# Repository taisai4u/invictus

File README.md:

# Invictus Flight Computer
A rocket flight computer capable of real-time sensor fusion, state estimation, and autonomous flight control.

Records absolute orientation during the duration of a rocket's flight

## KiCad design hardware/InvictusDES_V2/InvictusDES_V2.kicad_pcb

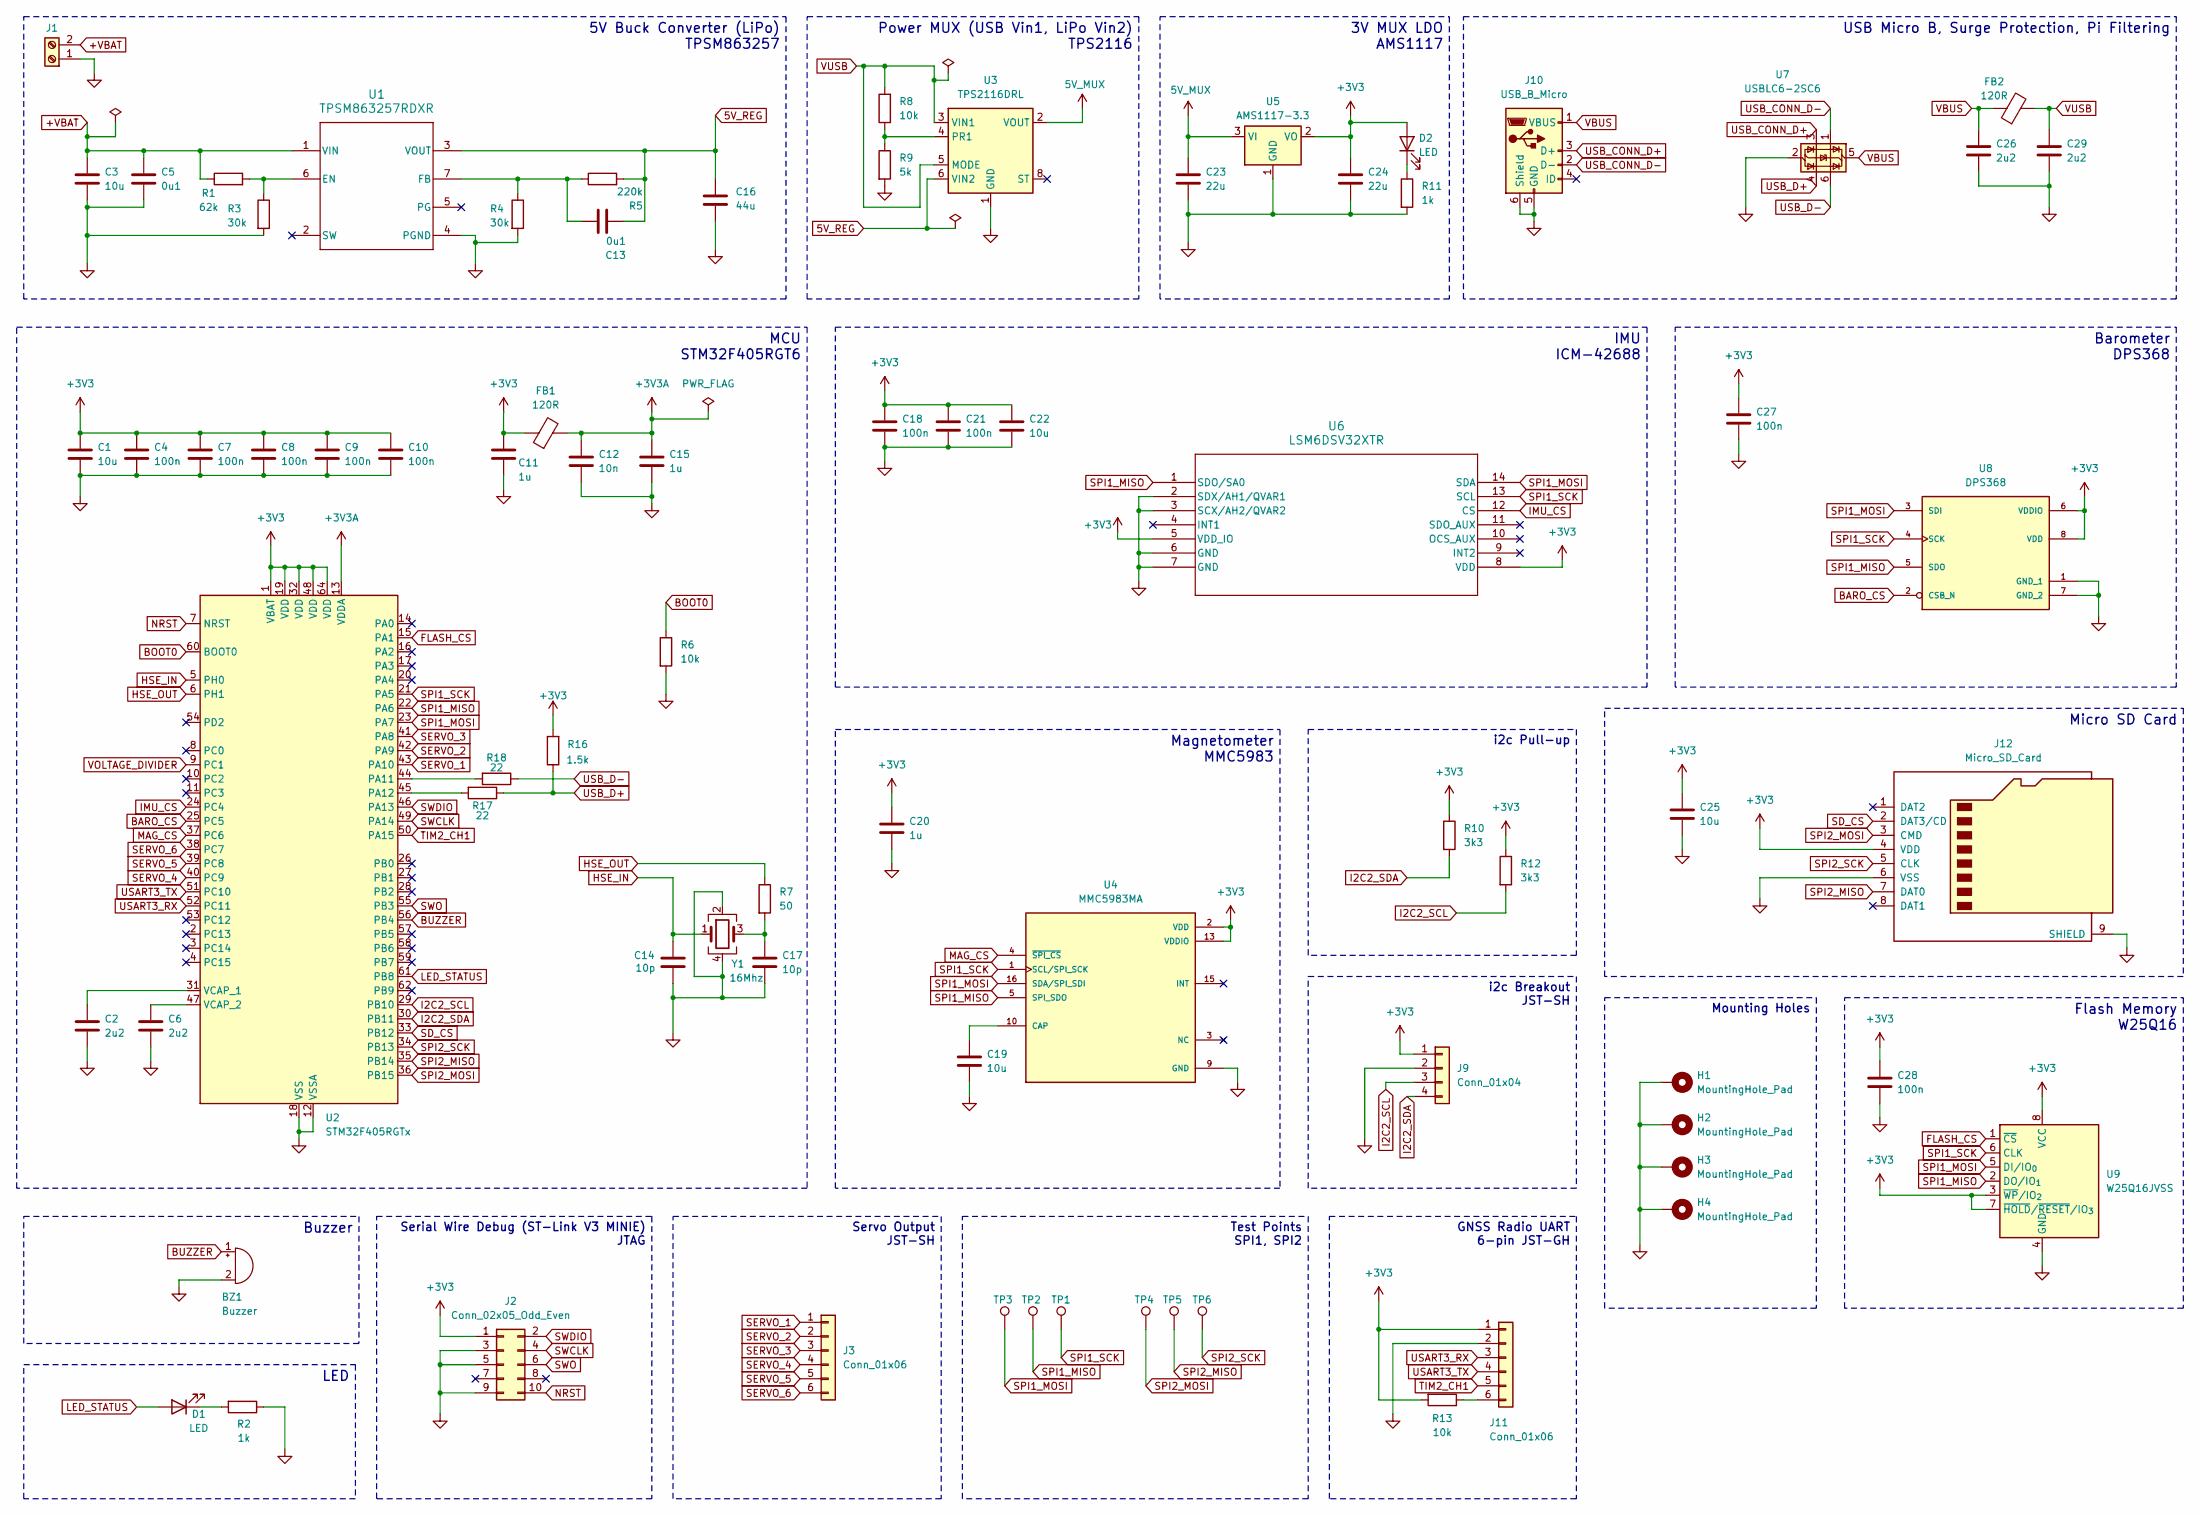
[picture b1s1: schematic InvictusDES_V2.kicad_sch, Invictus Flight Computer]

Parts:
BZ1: Buzzer; Buzzer_Murata_PKMCS0909E
C1, C3, C19: 10u; C_0603_1608Metric
C2, C6: 2u2; C_0603_1608Metric
C4, C7, C8, C9, C10, C18, C27, C28: 100n; C_0402_1005Metric
C5, C13: 0u1; C_0402_1005Metric
C11, C15, C20: 1u; C_0603_1608Metric
C12: 10n; C_0402_1005Metric
C14, C17: 10p; C_0603_1608Metric
C16: 44u; C_0402_1005Metric
C21: 100n; C_0603_1608Metric
C22, C25: 10u; C_0402_1005Metric
C23, C24: 22u; C_0805_2012Metric
C26, C29: 2u2; C_0402_1005Metric
D1, D2: LED; LED_0603_1608Metric
FB1, FB2: 120R; L_0603_1608Metric
H1, H2, H3, H4: MountingHole_Pad; MountingHole_2.2mm_M2
J1: Screw_Terminal_01x02; TerminalBlock_Phoenix_PT-1,5-2-5.0-H_1x02_P5.00mm_Horizontal
J2: Conn_02x05_Odd_Even; PinHeader_2x05_P1.27mm_Vertical
J3, J11: Conn_01x06; JST_SH_BM06B-SRSS-TB_1x06-1MP_P1.00mm_Vertical
J9: Conn_01x04; JST_SH_BM04B-SRSS-TB_1x04-1MP_P1.00mm_Vertical
J10: USB_B_Micro; USB_Micro-B_Molex-105017-0001
J12: Micro_SD_Card; microSD_HC_Molex_104031-0811
R1: 62k; R_0603_1608Metric
R2, R11: 1k; R_0603_1608Metric
R3, R4: 30k; R_0603_1608Metric
R5: 220k; R_0603_1608Metric
R6, R8, R13: 10k; R_0603_1608Metric
R7: 50; R_0603_1608Metric
R9: 5k; R_0603_1608Metric
R10, R12: 3k3; R_0603_1608Metric
R16: 1.5k; R_0603_1608Metric
R17, R18: 22; R_0402_1005Metric
TP1: TestPoint; TestPoint_Keystone_5000-5004_Miniature
TP2, TP3, TP4, TP5, TP6: TestPoint; TestPoint_Pad_D1.0mm
U1: TPSM863257RDXR; RDX0007A-MFG
U2: STM32F405RGTx; LQFP-64_10x10mm_P0.5mm
U3: TPS2116DRL; SOT-583-8
U4: MMC5983MA; PQFN50P300X300X100-16N; PARTREV A
U5: AMS1117-3.3; SOT-223-3_TabPin2
U6: LSM6DSV32XTR; LGA-14L_2p5X3p0X0p86_STM
U7: USBLC6-2SC6; SOT-23-6
U8: DPS368; LGA8S145X65P2X4_200X250X110-V
U9: W25Q16JVSS; SOIC-8_5.3x5.3mm_P1.27mm
Y1: 16Mhz; Crystal_SMD_3225-4Pin_3.2x2.5mm

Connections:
5V_MUX: C23.1, U3.2 (VOUT), U3.7 (VOUT), U5.3 (VI)
5V_REG: C13.2, C16.2, R5.2, U1.3 (VOUT), U3.6 (VIN2)
+3V3: C1.1, C4.1, C7.1, C8.1, C9.1, C10.1, C11.1, C18.1, C20.1, C21.1, C22.1, C24.1, C25.1, C27.1, C28.1, D2.2 (A), FB1.1, J2.1, J9.1, J11.1, J12.4 (VDD), R10.1, R12.1, R13.2, R16.2, U2.1 (VBAT), U2.19 (VDD), U2.32 (VDD), U2.48 (VDD), U2.64 (VDD), U4.2 (VDD), U4.13 (VDDIO), U5.2 (VO), U6.5 (VDD_IO), U6.8 (VDD), U8.6 (VDDIO), U8.8 (VDD), U9.3 (~WP/IO_{2}), U9.7 (~HOLD/~RESET/IO_{3}), U9.8 (VCC)
+3V3A: C12.1, C15.1, FB1.2, U2.13 (VDDA)
+VBAT: C3.1, C5.1, J1.2, R1.1, U1.1 (VIN)
BARO_CS: U2.25 (PC5), U8.2 (CSB_N)
BOOT0: R6.1, U2.60 (BOOT0)
BUZZER: BZ1.1 (+), U2.56 (PB4)
FLASH_CS: U2.15 (PA1), U9.1 (~CS)
GND: BZ1.2 (-), C1.2, C2.2, C3.2, C4.2, C5.2, C6.2, C7.2, C8.2, C9.2, C10.2, C11.2, C12.2, C14.2, C15.2, C16.1, C17.2, C18.2, C19.2, C20.2, C21.2, C22.2, C23.2, C24.2, C25.2, C26.2, C27.2, C28.2, C29.2, H1.1, H2.1, H3.1, H4.1, J1.1, J2.3, J2.5, J2.9, J9.2, J10.5 (GND), J10.6 (Shield), J11.2, J12.6 (VSS), J12.9 (SHIELD), R2.1, R3.2, R4.2, R6.2, R9.2, R11.2, U1.4 (PGND), U2.12 (VSSA), U2.18 (VSS), U2.63 (VSS), U3.1 (GND), U4.9 (GND), U4.11 (GND), U5.1 (GND), U6.2 (SDX/AH1/QVAR1), U6.3 (SCX/AH2/QVAR2), U6.6 (GND), U6.7 (GND), U7.2 (GND), U8.1 (GND_1), U8.7 (GND_2), U9.4 (GND), Y1.2, Y1.4
HSE_IN: C14.1, U2.5 (PH0), Y1.1
HSE_OUT: R7.1, U2.6 (PH1)
I2C2_SCL: J9.3, R12.2, U2.29 (PB10)
I2C2_SDA: J9.4, R10.2, U2.30 (PB11)
IMU_CS: U2.24 (PC4), U6.12 (CS)
LED_STATUS: D1.2 (A), U2.61 (PB8)
MAG_CS: U2.37 (PC6), U4.4 (~SPI_CS)
NRST: J2.10, U2.7 (NRST)
unnamed: C17.1, R7.2, Y1.3
unnamed: D1.1 (K), R2.2
unnamed: D2.1 (K), R11.1
unnamed: J11.6, R13.1
unnamed: R1.2, R3.1, U1.6 (EN)
unnamed: C13.1, R4.1, R5.1, U1.7 (FB)
unnamed: R18.2, U2.44 (PA11)
unnamed: R17.2, U2.45 (PA12)
unnamed: C2.1, U2.31 (VCAP_1)
unnamed: C6.1, U2.47 (VCAP_2)
unnamed: R8.1, R9.1, U3.4 (PR1)
unnamed: C19.1, U4.10 (CAP)
SD_CS: J12.2 (DAT3/CD), U2.33 (PB12)
SERVO_1: J3.1, U2.43 (PA10)
SERVO_2: J3.2, U2.42 (PA9)
SERVO_3: J3.3, U2.41 (PA8)
SERVO_4: J3.4, U2.40 (PC9)
SERVO_5: J3.5, U2.39 (PC8)
SERVO_6: J3.6, U2.38 (PC7)
SPI1_MISO: TP2.1, U2.22 (PA6), U4.5 (SPI_SDO), U6.1 (SDO/SA0), U8.5 (SDO), U9.2 (DO/IO_{1})
SPI1_MOSI: TP3.1, U2.23 (PA7), U4.16 (SDA/SPI_SDI), U6.14 (SDA), U8.3 (SDI), U9.5 (DI/IO_{0})
SPI1_SCK: TP1.1, U2.21 (PA5), U4.1 (SCL/SPI_SCK), U6.13 (SCL), U8.4 (SCK), U9.6 (CLK)
SPI2_MISO: J12.7 (DAT0), TP5.1, U2.35 (PB14)
SPI2_MOSI: J12.3 (CMD), TP4.1, U2.36 (PB15)
SPI2_SCK: J12.5 (CLK), TP6.1, U2.34 (PB13)
SWCLK: J2.4, U2.49 (PA14)
SWDIO: J2.2, U2.46 (PA13)
SWO: J2.6, U2.55 (PB3)
TIM2_CH1: J11.5, U2.50 (PA15)
USART3_RX: J11.3, U2.52 (PC11)
USART3_TX: J11.4, U2.51 (PC10)
USB_CONN_D+: J10.3 (D+), U7.3 (I/O2)
USB_CONN_D-: J10.2 (D-), U7.1 (I/O1)
USB_D+: R16.1, R17.1, U7.4 (I/O2)
USB_D-: R18.1, U7.6 (I/O1)
VBUS: C26.1, FB2.1, J10.1 (VBUS), U7.5 (VBUS)
VOLTAGE_DIVIDER: U2.9 (PC1)
VUSB: C29.1, FB2.2, R8.2, U3.3 (VIN1), U3.5 (MODE)

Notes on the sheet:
Power MUX (USB Vin1, LiPo Vin2) TPS2116
i2c Breakout JST-SH
5V Buck Converter (LiPo) TPSM863257
GNSS Radio UART 6-pin JST-GH
Serial Wire Debug (ST-Link V3 MINIE) JTAG
Buzzer
3V MUX LDO AMS1117
Micro SD Card
Mounting Holes
LED
MCU STM32F405RGT6
Magnetometer MMC5983
USB Micro B, Surge Protection, Pi Filtering
Flash Memory W25Q16
Barometer DPS368
IMU ICM-42688
Test Points SPI1, SPI2
Servo Output JST-SH
i2c Pull-up

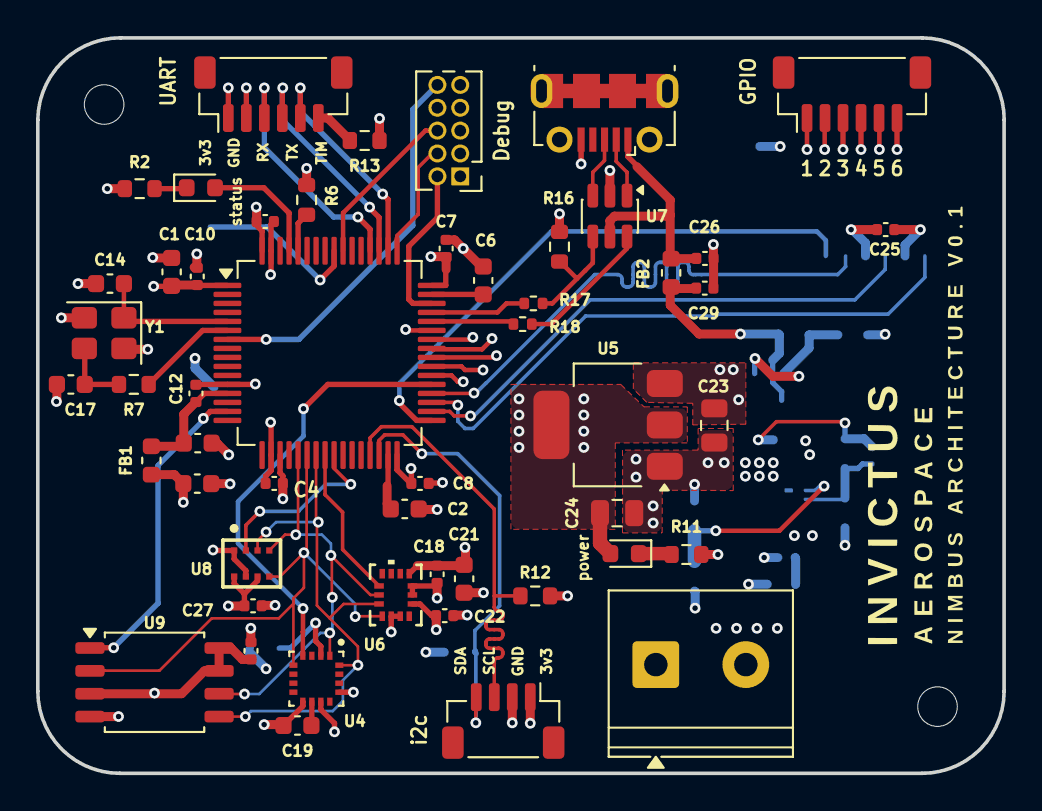
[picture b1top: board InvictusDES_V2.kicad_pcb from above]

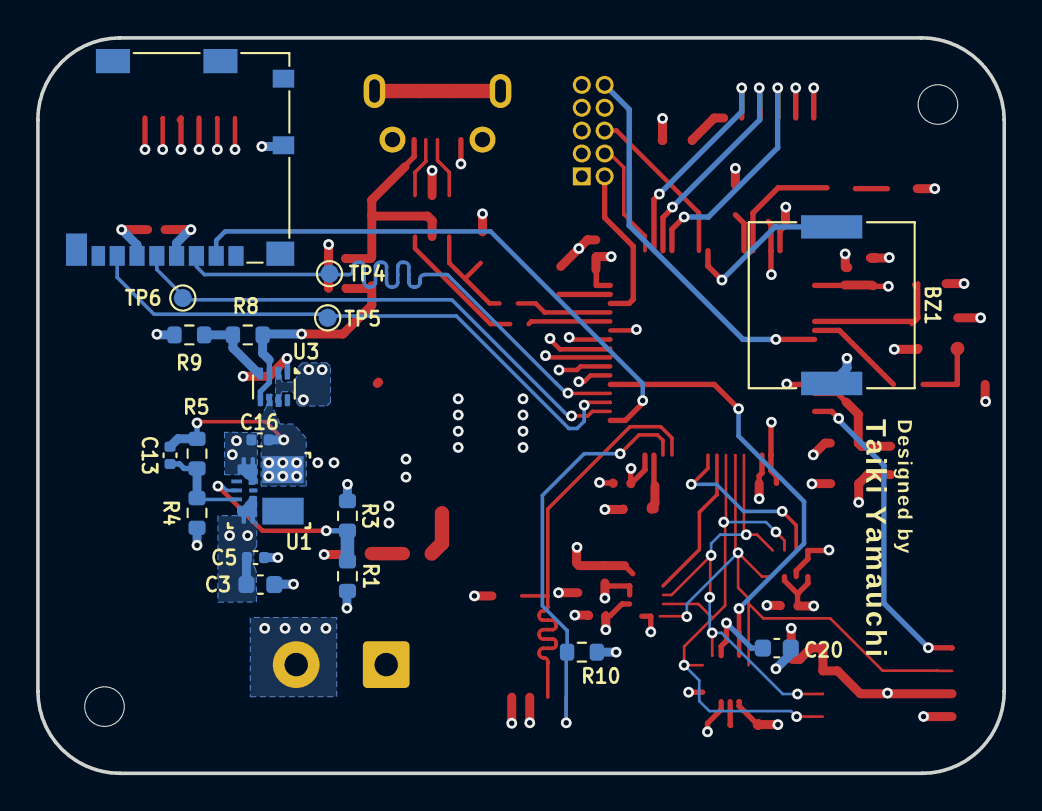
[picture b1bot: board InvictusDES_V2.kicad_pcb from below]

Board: 4 copper layers, 53.7 x 40.9 mm, 72 parts (19 on the bottom side), 55 nets.

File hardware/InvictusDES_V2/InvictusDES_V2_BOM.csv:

InvictusDES_V2_BOM,,,,,,,,
Id,Designator,Footprint,Quantity,Designation,Supplier,Manufacturer,MPN,Notes
1,U6,LGA-14L_2p5X3p0X0p86_STM,1,LSM6DSV32XTR,Digikey,STMicroelectronics,LSM6DSV32XTR,
2,"D1,D2",LED_0603_1608Metric,2,LED,Digikey,Yongyu Optoelectronics,YY0603GR-NZ1S0-T2AR4,Green
3,"C6,C2",C_0603_1608Metric,2,2u2,,,,
4,"C22,C25",C_0402_1005Metric,2,10u,,,,
5,"C18,C10,C7,C27,C9,C8,C4,C28",C_0402_1005Metric,8,100n,,,,
6,"TP2,TP3,TP6,TP1,TP5,TP4",TestPoint_Pad_D1.0mm,6,TestPoint,,,,Made on pcb
7,C12,C_0402_1005Metric,1,10n,,,,
8,R16,R_0603_1608Metric,1,1.5k,,,,
9,"C14,C17",C_0603_1608Metric,2,12u,,,,
10,"C29,C26",C_0402_1005Metric,2,2u2,,,,
11,"C20,C11,C15",C_0603_1608Metric,3,1u,,,,
12,"C1,C19,C3",C_0603_1608Metric,3,10u,,,,
13,"C24,C23",C_0805_2012Metric,2,22u,,,,
14,U4,PQFN50P300X300X100-16N,1,MMC5983MA,Digikey,Memsic Inc.,MMC5983MA,
15,"R17,R18",R_0402_1005Metric,2,22,,,,
16,"R2,R11",R_0603_1608Metric,2,1k,,,,
17,J9,Molex_PicoBlade_53047-0410_1x04_P1.25mm_Vertical,1,Conn_01x04,Digikey,Molex,530470410,
18,R7,R_0603_1608Metric,1,50,,,,
19,U2,LQFP-64_10x10mm_P0.5mm,1,STM32F405RGTx,Digikey,STMicroelectronics,STM32F405RGT7TR,
20,U8,LGA8S145X65P2X4_200X250X110-V,1,DPS368,Not Available ,Not Available ,Not Available ,Not Available
21,J3,JST_SH_BM06B-SRSS-TB_1x06-1MP_P1.00mm_Vertical,1,Conn_01x06,Digikey,JST Sales America Inc.,BM06B-SRSS-TB,
22,"R10,R12",R_0603_1608Metric,2,3k3,,,,
23,J1,"TerminalBlock_Phoenix_PT-1,5-2-5.0-H_1x02_P5.00mm_Horizontal",1,Screw_Terminal_01x02,Digikey,Phoenix Contact,1729018,
24,J2,PinHeader_2x05_P1.27mm_Vertical,1,Conn_02x05_Odd_Even,Mouser,Mill-Max,852-40-006-10-001000,"Only exists as a 2x6, in even numbers of pins in each row"
25,J11,Molex_PicoBlade_53047-0610_1x06_P1.25mm_Vertical,1,Conn_01x06,Digikey,Molex,530470610,
26,J10,USB_Micro-B_Molex-105017-0001,1,USB_B_Micro,Digikey,Molex,1050170001,
27,"R6,R13,R8",R_0603_1608Metric,3,10k,,,,
28,U7,SOT-23-6,1,USBLC6-2SC6,Digikey,STMicroelectronics,USBLC6-2SC6,
29,C21,C_0603_1608Metric,1,100n,,,,
30,U5,SOT-223-3_TabPin2,1,AMS1117-3.3,Digikey,EVVO,AMS1117-3.3,
31,"FB2,FB1",L_0603_1608Metric,2,120R,,,,
32,Y1,Crystal_SMD_3225-4Pin_3.2x2.5mm,1,16Mhz,,,,Find specific crystal
33,U9,SOIC-8_5.3x5.3mm_P1.27mm,1,W25Q16JVSS,Digikey,Winbond Electronics,W25Q16JVSSIQ TR,
34,R1,R_0603_1608Metric,1,62k,,,,
35,U3,SOT-583-8,1,TPS2116DRL,Digikey,Texas Instruments,TPS2116DRLR,
36,BZ1,Buzzer_Murata_PKMCS0909E,1,Buzzer,Digikey,Murata Electronics,PKMCS0909E48H0-R1,
37,R9,R_0603_1608Metric,1,5k,,,,
38,J12,microSD_HC_Molex_104031-0811,1,Micro_SD_Card,Digikey,Molex,1040310811,Only 10 in stock
39,"R3,R4",R_0603_1608Metric,2,30k,,,,
40,"C13,C5",C_0402_1005Metric,2,0u1,,,,
41,U1,RDX0007A-MFG,1,TPSM863257RDXR,Digikey,Texas Instruments,TPSM863257RDXR,
42,R5,R_0603_1608Metric,1,220k,,,,
43,C16,C_0402_1005Metric,1,44u,,,,

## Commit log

2026-01-23 Add README file
2026-01-25 README
2026-01-25 Create sensor abstraction layer mirroring C++ structure
2026-02-20 KiCad files for Invictus V1
2026-02-20 Added v1 Flight computer PCB files
2026-02-21 csv sample file
2026-02-21 add tauri app
2026-02-21 list and load csv
2026-02-21 viz stuff
2026-02-21 basic pyqt app with charts
2026-02-21 fix lag when playback, extract playback controls to component
2026-02-21 mission stats
2026-02-22 euler integrator and mission view
2026-02-22 subtract gravity to get real acceleration
2026-02-22 flight data generator
2026-02-25 add flight simulation interface
2026-02-25 set up filter
2026-02-25 simulate rocket and plot
2026-02-25 move to script
2026-02-25 magnetometer, but finding the correct H matrix given the correction of orientation to world frame is too complex (2 rotations)
2026-02-25 remove g from state
2026-02-25 FILTER WORKS
2026-02-25 plot log likelihood and NEES
2026-02-25 reduce gps altitude accuracy, filter using altimeter
2026-02-26 simulate transsonic pressure spike, reject outlier measurements using mahalanobis distance
2026-02-26 factor random forces into imu measurement
2026-02-26 plotting changes
2026-02-26 intialize filter with all initial measurements at once
2026-02-26 mahalanobis
2026-02-27 time-invariant simulation
2026-02-27 print nees separately
2026-02-27 rk4 integration
2026-02-27 fix NEES by increasing gyro process noise by 40x (to be due to possible nonlinearity at high angular rates), and initialize with lower covar for biases
2026-03-01 decouple constants from all methods
2026-03-01 arduino
2026-03-02 filter connected imu
2026-03-02 detect if imu is static
2026-03-02 filter orientation using accelerometer
2026-03-02 fix nans, add axes and min viewport to visualization
2026-03-02 ZUPT
2026-03-02 empirically determine noise values (record std when static)
2026-03-03 visualize NIS and gyro biases, more accurate derivation of R matrices
2026-03-03 adaptive r experiment
2026-03-03 factor accel biases into accel updates, remove normalization to improve linearity. all NIS consistent except for ZUPT
2026-03-03 incorporate difference between g and a_m into R for accel updates
2026-03-03 find baseline (for static IMU) R values for accel, mag, zupt
2026-03-04 goofy ahh tuning
2026-03-04 use bias walk calculated from allan variance
2026-03-04 more frequent updates giving better consistency
2026-03-09 filter tutorial in matlab
2026-03-10 filter working on sample quadcopter data!
2026-03-10 function for evaluating filter
2026-03-10 read data from arduino
2026-03-24 updated PCB, pre-DRC, new IMU, all traces routed for now
2026-03-24 Test Points, spi bus tidying, and fab prep
2026-03-24 added all active components into BOM
2026-03-25 new imu, organized GPIOs, new sensor layout
2026-03-26 finished PCB, 0 DRC violations, 'logo' made.
2026-03-26 Adjusted i2c, GPIO breakouts, DRC-passed
2026-03-26 modified copper pours, tidied up layout
2026-03-27 Connectors made to JST-SH, aligned silkscreen designators and connectors
2026-03-29 Peripherals finalized, Silkscreen mods, updated schematic
2026-03-29 make important coordinate system for IMU readings: invert IMU readings since MATLAB imuSensor gives negative of specific force
2026-03-29 add noise back to filter sim
2026-03-29 keep-out zones for IMU, Mag filled.
2026-03-29 visualization for orientation filter
2026-03-29 disable accel for now
2026-03-29 calibrate bno, sensor updates work much better now
2026-03-30 show stats in visualizer top right
2026-03-30 fix spin rate in flight generation
2026-03-30 Layout tidying. Labeled all GPIOs. 0 DRC violations.
